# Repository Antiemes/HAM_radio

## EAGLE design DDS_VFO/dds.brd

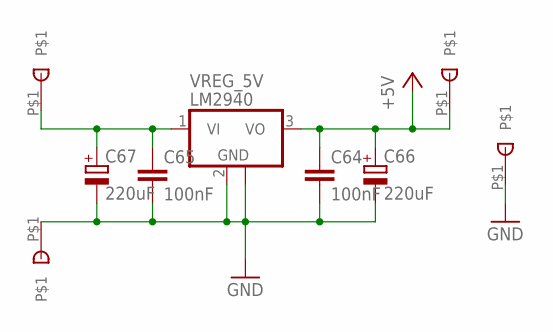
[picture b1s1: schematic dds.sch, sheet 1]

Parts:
C64, C65: 100nF; C0603
C66, C67: 220uF; CT7343
U$3, U$8: SINGLE_SMD_CONN_2.5X3.5; SMD_CONN_2.5X3.5
U$22, U$23: SINGLE_SMD_CONN_1.5X1.5; SMD_CONN_1.5X1.5
VREG_5V: LM2940; SOT223

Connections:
+5V: C64.1, C66.+, U$22.P$1, VREG_5V.3 (VO); also elsewhere on the board
GND: C64.2, C65.2, C66.-, C67.-, U$3.P$1, U$23.P$1, VREG_5V.2 (GND), VREG_5V.4 (GND); also elsewhere on the board
VCC: C65.1, C67.+, U$8.P$1, VREG_5V.1 (VI); also elsewhere on the board

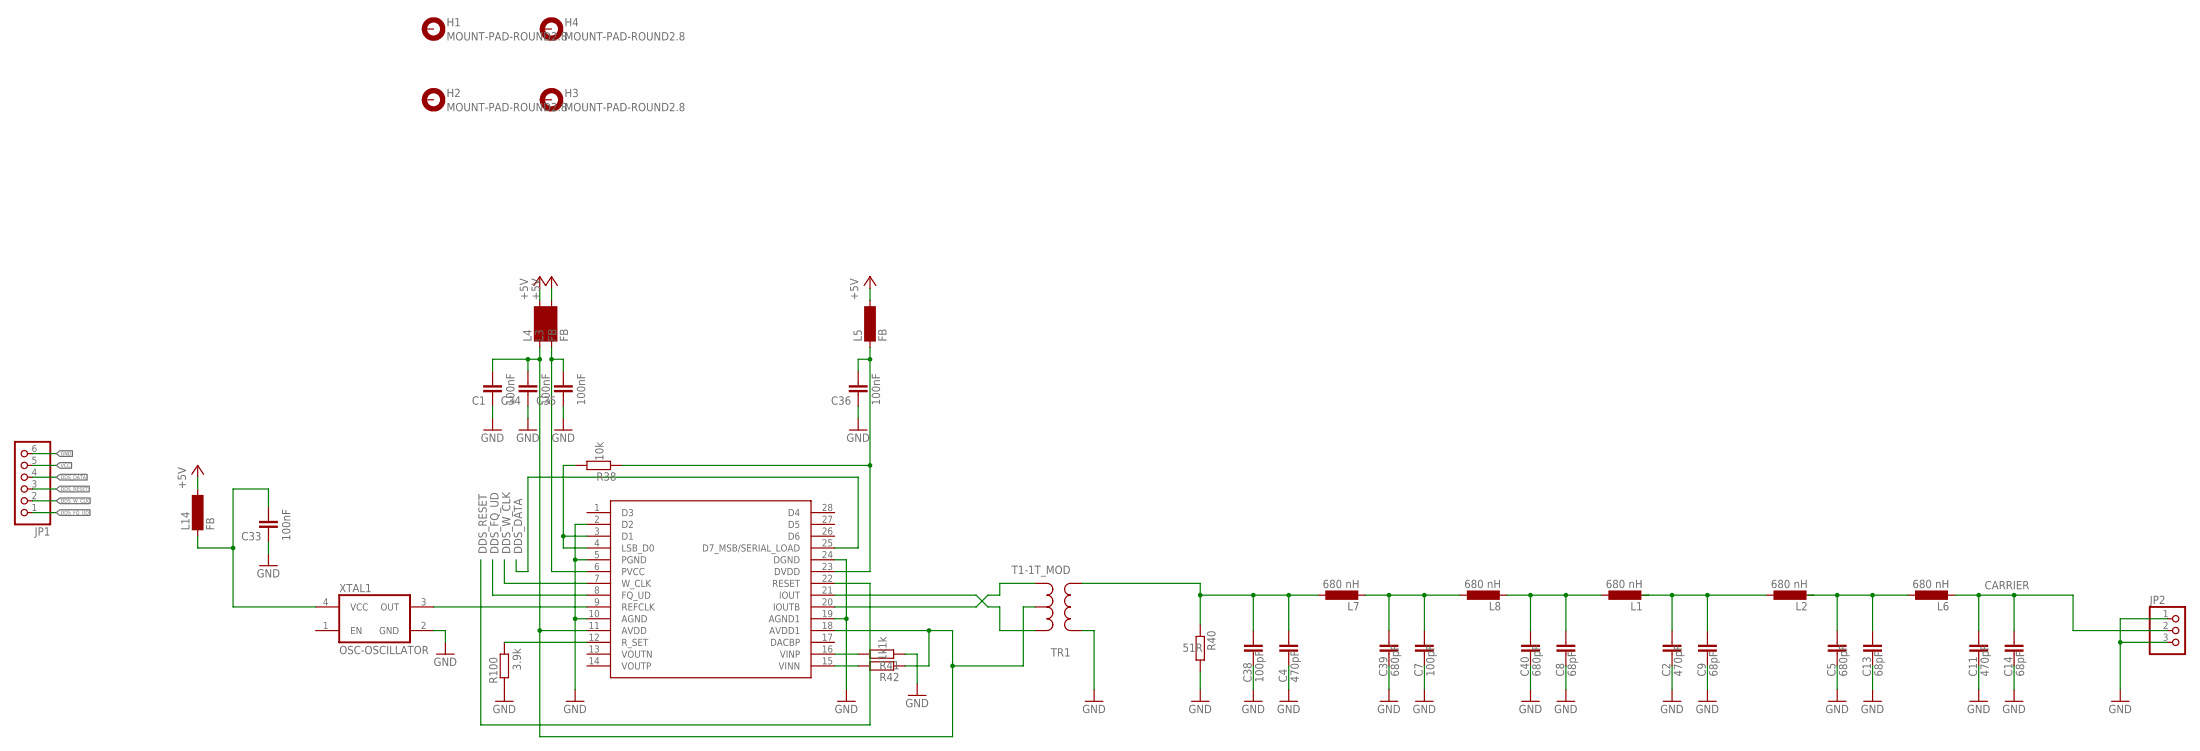
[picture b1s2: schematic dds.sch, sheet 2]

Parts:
C1, C33, C34, C35, C36: 100nF; C0603K
C2, C4, C11: 470pF; C1206
C5, C39, C40: 680pF; C1206
C7, C38: 100pF; C1206
C8, C9, C13, C14: 68pF; C1206
H1, H2, H3, H4: MOUNT-PAD-ROUND2.8; 2,8-PAD
JP1: PINHD-1X6; 1X06
JP2: PINHD-1X3; 1X03
L1, L2, L6, L7, L8: 680 nH; L1812
L3, L4, L5, L14: FB; SM-1206
R38: 10k; R0603
R40: 51R; R0603
R41, R42: 1k; R0603
R100: 3.9k; R0603
TR1: T1-1T_MOD; KK81_MOD
U$9: AD9851BR; TSSOP28
XTAL1: OSC-OSCILLATOR; OSCILLATOR_7X5_SMD

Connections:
30MHZ: U$9.9 (REFCLK), XTAL1.3 (OUT)
+5V: L3.2, L4.2, L5.2, L14.2; also elsewhere on the board
AVDD: C1.2, C34.2, L4.1, R42.1, TR1.5 (ST), U$9.11 (AVDD), U$9.18 (AVDD1)
DDSOUT: C4.2, C38.2, L7.1, R40.1, TR1.3 (P2)
DDS_DATA: JP1.4, U$9.25 (D7_MSB/SERIAL_LOAD)
DDS_FQ_UD: JP1.1, U$9.8 (FQ_UD)
DDS_RESET: JP1.3, U$9.22 (RESET)
DDS_W_CLK: JP1.2, U$9.7 (W_CLK)
DVDD: C36.2, L5.1, R38.1, U$9.23 (DVDD)
FILTERED: C11.2, C14.2, JP2.2, L6.2
GND: C1.1, C2.1, C4.1, C5.1, C7.1, C8.1, C9.1, C11.1, C13.1, C14.1, C33.1, C34.1, C35.1, C36.1, C38.1, C39.1, C40.1, JP1.6, JP2.1, JP2.3, R40.2, R41.1, R100.1, TR1.1, U$9.2 (D2), U$9.5 (PGND), U$9.10 (AGND), U$9.19 (AGND1), U$9.24 (DGND), XTAL1.2 (GND); also elsewhere on the board
unnamed: C8.2, C40.2, L1.1, L8.2
unnamed: C2.2, C9.2, L1.2, L2.1
unnamed: TR1.4 (S2), U$9.20 (IOUTB)
unnamed: C5.2, C13.2, L2.2, L6.1
unnamed: R38.2, U$9.3 (D1), U$9.4 (LSB_D0)
unnamed: TR1.6 (S1), U$9.21 (IOUT)
unnamed: R41.2, U$9.16 (VINP)
unnamed: R42.2, U$9.15 (VINN)
unnamed: C7.2, C39.2, L7.2, L8.1
unnamed: R100.2, U$9.12 (R_SET)
PVCC: C35.2, L3.1, U$9.6 (PVCC)
VCC: JP1.5; also elsewhere on the board
VCC_OSC: C33.2, L14.1, XTAL1.4 (VCC)

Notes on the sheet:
CARRIER
DDS_RESET
DDS_FQ_UD
DDS_W_CLK
DDS_DATA

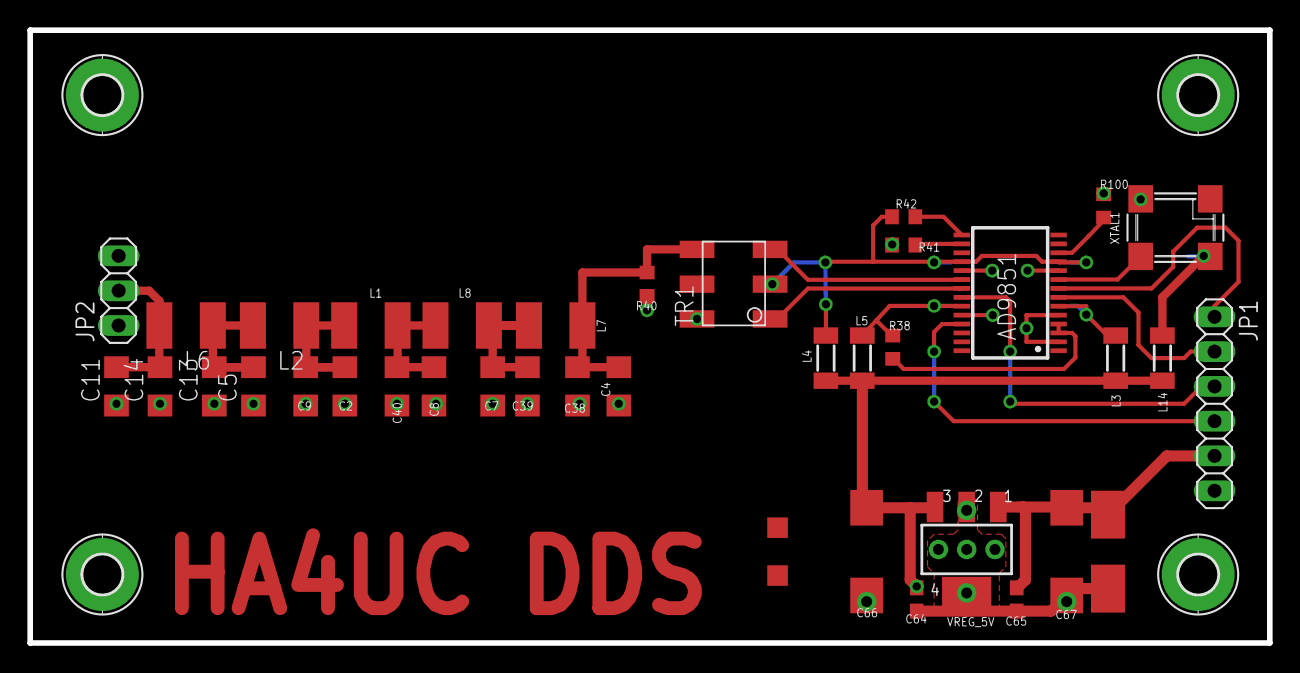
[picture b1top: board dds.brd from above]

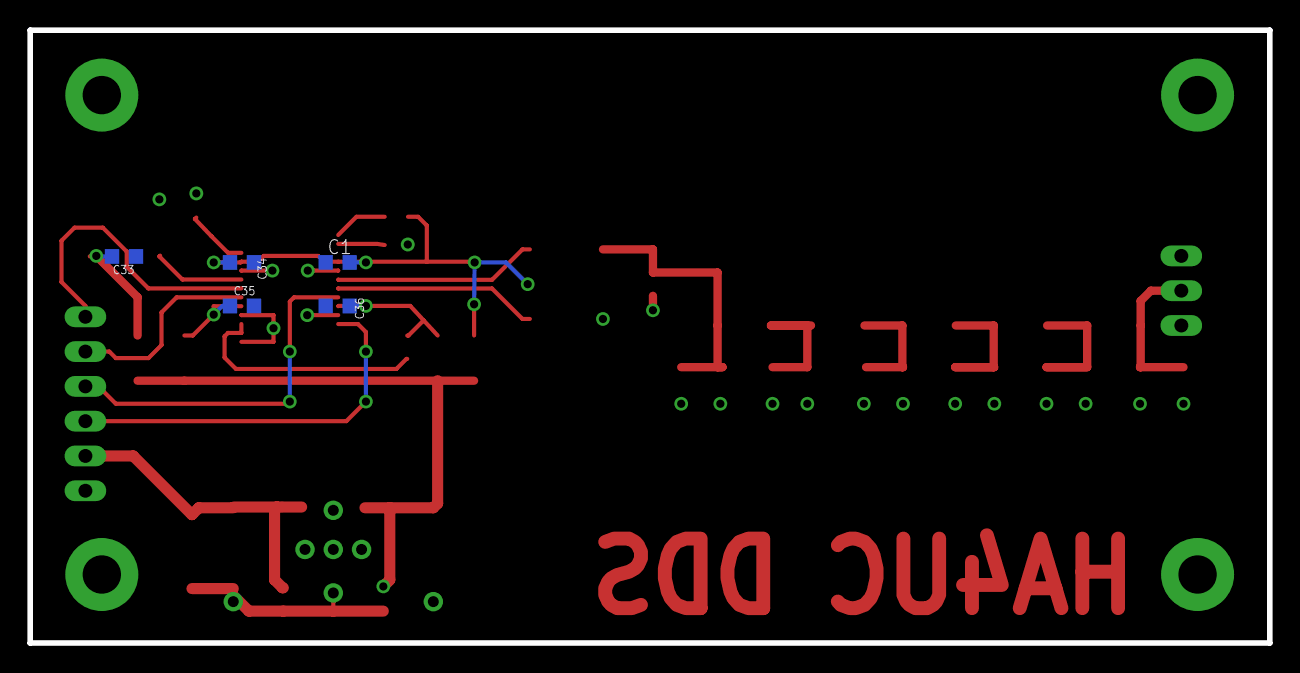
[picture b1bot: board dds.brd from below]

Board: 2 copper layers, 90.5 x 44.7 mm, 49 parts (5 on the bottom side), 24 nets.

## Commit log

2020-03-12 DDS VFO added.
2020-03-18 Almost done.
